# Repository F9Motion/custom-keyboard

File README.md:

# BEST KEYBOARD PROJECT EVER!!!

hey! this is text explaining what my awesome project is :)

here's an AWESOME screenshoot of my keyboard in action!

## HOW THIS WAS MADE

this custom keyboard was designed in [KiCad](https://www.kicad.org/) for the PCB, modeled in [Blender](https://www.blender.org/) for the 3D-printed enclosure, and runs on [CircuitPython](https://circuitpython.org/) :D

# Heres how to setup and flash the project :)
Clone the repository to your device:
git clone **https://github.com/f9motion/custom-keyboard**

Connect your microcontroller board in BOOTLOADER mode via USB

Copy the CircuitPython firmware files and keymap script to your device drive
firmware in my github repositorie ~~https://github.com/f9motion/custom-keyboard~~

Disconnect, plug in, and type away!
and be joyous!
# Sreenshots
**Schematic in KiCad:**

**PCB editor:**

**Case in blender 3.6**

#Bill Of Materials (BOM)

| Object name    | Cost   | Link                                                                                                                                                       |
|----------------|--------|------------------------------------------------------------------------------------------------------------------------------------------------------------|
| Soldering iron | $12.76 | https://aliexpress.ru/item/33052506638.html?spm=a2g2w.cart.cart_split.2.57294aa6AC23aP&sku_id=12000032616421342                                            |
| Stabilizers    | $9.00  | https://aliexpress.ru/item/1005006528731543.html?spm=a2g2w.cart.cart_split.4.182a4aa6UvSz3j&sku_id=12000039275106552                                       |
| Switchs        | $24.4  | https://aliexpress.ru/item/1005009446526905.html?spm=a2g2w.cart.cart_split.2.36c84aa6Uj1yYg&sku_id=12000049127519972                                       |
| Diodes x3      | $6.12  | https://aliexpress.ru/item/1005008957914820.html?spm=a2g2w.cart.cart_split.8.36c84aa6Uj1yYg&sku_id=12000047366893545                                       |
| Pico           | $2.2   | https://aliexpress.ru/item/1005003371056277.html?sku_id=12000035247643698                                                                                  |
| Solder         | $4.36  | https://aliexpress.ru/item/32889029087.html?shpMethod=AE_CN_SUPER_ECONOMY_G&sku_id=12000036063038181&spm=a2g2w.productlist.search_results.0.5a2f3831nIBAqg |
| Print PCB | $59.19 | 
| Filament price for 3d print  |                                        | WARNING: All price took from Bambu Studio!!!                                                                 |
| **Object name**     | **Weight** | **Cost**                                                                                                                                          |
| Case.step           | 153.95g    | $2.77                                                                                                                                             |
| keycaps.step        | 129.47g    | $2.59                                                                                                                                             |
| switch holder.step  | 29.67g     | $0.53                                                                                                                                             |
| TOTAL OF ALL: | | $123.92 |

AI DISCLOSURE
Ai helped me to now microcontroller name and how much u in shift ctrl etc (u is size) and helped to write firmware

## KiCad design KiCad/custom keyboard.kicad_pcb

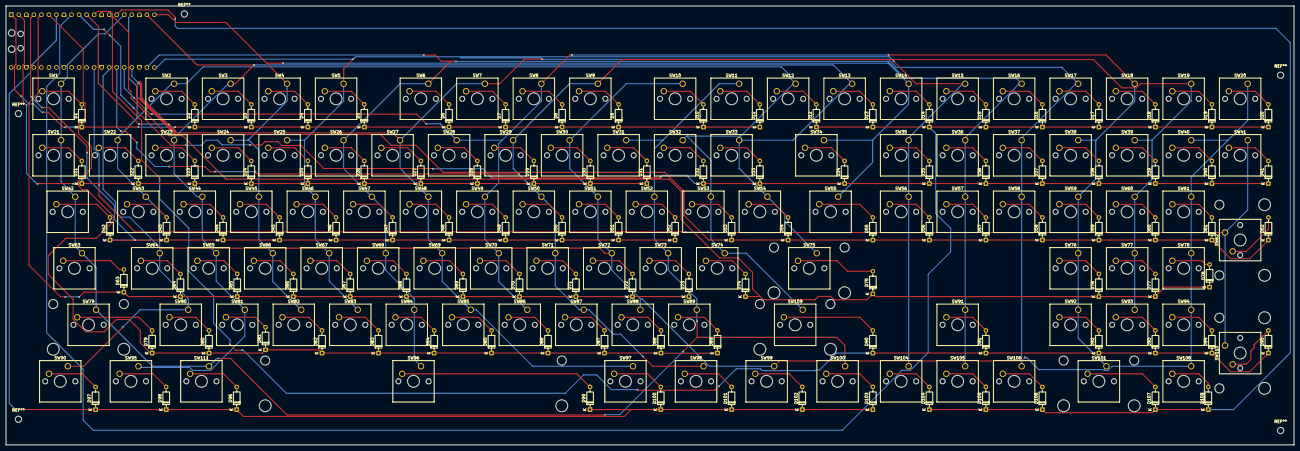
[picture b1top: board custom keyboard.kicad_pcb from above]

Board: 2 copper layers, 434.2 x 148.0 mm, 217 parts (1 on the bottom side), 131 nets.

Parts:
A1: RaspberryPi_Pico; RaspberryPi_Pico_Common_Unspecified
D1, D2, D3, D4, D5, D6, D7, D8, D9, D10, D11, D12, D13, D14, D15, D16, D17, D18, D19, D20, D21, D22, D23, D24, D25, D26, D27, D28, D29, D30, D31, D32, D33, D34, D35, D36, D37, D38, D39, D40, D41, D42, D43, D44, D45, D46, D47, D48, D49, D50, D51, D52, D53, D54, D55, D56, D57, D58, D59, D60, D61, D62, D63, D64, D65, D66, D67, D68, D69, D70, D71, D72, D73, D74, D75, D76, D77, D78, D79, D80, D81, D82, D83, D84, D85, D86, D87, D88, D89, D90, D91, D92, D93, D94, D95, D96, D97, D98, D99, D100, D101, D102, D103, D104, D105, D106, D107, D108: 1N4148; D_DO-35_SOD27_P7.62mm_Horizontal
SW1, SW2, SW3, SW4, SW5, SW6, SW7, SW8, SW9, SW10, SW11, SW12, SW13, SW14, SW15, SW16, SW17, SW18, SW19, SW20, SW21, SW22, SW23, SW24, SW25, SW26, SW27, SW28, SW29, SW30, SW31, SW32, SW33, SW34, SW35, SW36, SW37, SW38, SW39, SW40, SW41, SW43, SW44, SW45, SW46, SW47, SW48, SW49, SW50, SW51, SW52, SW53, SW54, SW56, SW57, SW58, SW59, SW60, SW61, SW64, SW65, SW66, SW67, SW68, SW69, SW70, SW71, SW72, SW73, SW74, SW76, SW77, SW78, SW80, SW81, SW82, SW83, SW84, SW85, SW86, SW87, SW88, SW89, SW91, SW92, SW93, SW94, SW104, SW105, SW106, SW108: SW_Push; SW_Cherry_MX_1.00u_PCB
SW42, SW55: SW_Push; SW_Cherry_MX_1.50u_PCB
SW62, SW101, SW110: SW_Push; SW_Cherry_MX_2.00u_PCB
SW63: SW_Push; SW_Cherry_MX_1.75u_PCB
SW75, SW79: SW_Push; SW_Cherry_MX_2.25u_PCB
SW90, SW95, SW97, SW98, SW99, SW100, SW111: SW_Push; SW_Cherry_MX_1.25u_PCB
SW96: SW_Push; SW_Cherry_MX_6.25u_PCB
SW109: SW_Push; SW_Cherry_MX_2.75u_PCB

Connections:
COL0: A1.16 (GPIO12), SW1.1, SW11.1, SW21.1, SW31.1, SW42.1, SW52.1, SW63.1, SW73.1, SW79.1, SW89.1, SW100.1, SW111.1
COL1: A1.17 (GPIO13), SW2.1, SW12.1, SW22.1, SW32.1, SW43.1, SW53.1, SW64.1, SW74.1, SW80.1, SW90.1, SW109.1
COL2: A1.19 (GPIO14), SW3.1, SW13.1, SW23.1, SW33.1, SW44.1, SW54.1, SW65.1, SW75.1, SW81.1, SW95.1
COL3: A1.20 (GPIO15), SW4.1, SW14.1, SW24.1, SW34.1, SW45.1, SW55.1, SW66.1, SW82.1
COL4: A1.21 (GPIO16), SW5.1, SW15.1, SW25.1, SW35.1, SW46.1, SW56.1, SW67.1, SW83.1, SW104.1
COL5: A1.22 (GPIO17), SW6.1, SW16.1, SW26.1, SW36.1, SW47.1, SW57.1, SW68.1, SW84.1, SW91.1, SW96.1, SW105.1
COL6: A1.24 (GPIO18), SW7.1, SW17.1, SW27.1, SW37.1, SW48.1, SW58.1, SW69.1, SW85.1, SW97.1, SW106.1
COL7: A1.25 (GPIO19), SW8.1, SW18.1, SW28.1, SW38.1, SW49.1, SW59.1, SW70.1, SW76.1, SW86.1, SW92.1, SW101.1
COL8: A1.26 (GPIO20), SW9.1, SW19.1, SW29.1, SW39.1, SW50.1, SW60.1, SW71.1, SW77.1, SW87.1, SW93.1, SW98.1
COL9: A1.27 (GPIO21), SW10.1, SW20.1, SW30.1, SW40.1, SW51.1, SW61.1, SW72.1, SW78.1, SW88.1, SW94.1, SW99.1, SW108.1
COL10: A1.29 (GPIO22), SW41.1, SW62.1, SW110.1
unnamed: D1.2 (A), SW1.2
unnamed: D2.2 (A), SW2.2
unnamed: D3.2 (A), SW3.2
unnamed: D4.2 (A), SW4.2
unnamed: D5.2 (A), SW5.2
unnamed: D6.2 (A), SW6.2
unnamed: D7.2 (A), SW7.2
unnamed: D8.2 (A), SW8.2
unnamed: D9.2 (A), SW9.2
unnamed: D10.2 (A), SW10.2
unnamed: D11.2 (A), SW11.2
unnamed: D12.2 (A), SW12.2
unnamed: D13.2 (A), SW13.2
unnamed: D14.2 (A), SW14.2
unnamed: D15.2 (A), SW15.2
unnamed: D16.2 (A), SW16.2
unnamed: D17.2 (A), SW17.2
unnamed: D18.2 (A), SW18.2
unnamed: D19.2 (A), SW19.2
unnamed: D20.2 (A), SW20.2
unnamed: D21.2 (A), SW21.2
unnamed: D22.2 (A), SW22.2
unnamed: D23.2 (A), SW23.2
unnamed: D24.2 (A), SW24.2
unnamed: D25.2 (A), SW25.2
unnamed: D26.2 (A), SW26.2
unnamed: D27.2 (A), SW27.2
unnamed: D28.2 (A), SW28.2
unnamed: D29.2 (A), SW29.2
unnamed: D30.2 (A), SW30.2
unnamed: D31.2 (A), SW31.2
unnamed: D32.2 (A), SW32.2
unnamed: D33.2 (A), SW33.2
unnamed: D34.2 (A), SW34.2
unnamed: D35.2 (A), SW35.2
unnamed: D36.2 (A), SW36.2
unnamed: D37.2 (A), SW37.2
unnamed: D38.2 (A), SW38.2
unnamed: D39.2 (A), SW39.2
unnamed: D40.2 (A), SW40.2
unnamed: D41.2 (A), SW41.2
unnamed: D42.2 (A), SW42.2
unnamed: D43.2 (A), SW43.2
unnamed: D44.2 (A), SW44.2
unnamed: D45.2 (A), SW45.2
unnamed: D46.2 (A), SW46.2
unnamed: D47.2 (A), SW47.2
unnamed: D48.2 (A), SW48.2
unnamed: D49.2 (A), SW49.2
unnamed: D50.2 (A), SW50.2
unnamed: D51.2 (A), SW51.2
unnamed: D52.2 (A), SW52.2
unnamed: D53.2 (A), SW53.2
unnamed: D54.2 (A), SW54.2
unnamed: D55.2 (A), SW55.2
unnamed: D56.2 (A), SW56.2
unnamed: D57.2 (A), SW57.2
unnamed: D58.2 (A), SW58.2
unnamed: D59.2 (A), SW59.2
unnamed: D60.2 (A), SW60.2
unnamed: D61.2 (A), SW61.2
unnamed: D62.2 (A), SW62.2
unnamed: D63.2 (A), SW63.2
unnamed: D64.2 (A), SW64.2
unnamed: D65.2 (A), SW65.2
unnamed: D66.2 (A), SW66.2
unnamed: D67.2 (A), SW67.2
unnamed: D68.2 (A), SW68.2
unnamed: D69.2 (A), SW69.2
unnamed: D70.2 (A), SW70.2
unnamed: D71.2 (A), SW71.2
unnamed: D72.2 (A), SW72.2
unnamed: D73.2 (A), SW73.2
unnamed: D74.2 (A), SW74.2
unnamed: D75.2 (A), SW75.2
unnamed: D76.2 (A), SW76.2
unnamed: D77.2 (A), SW77.2
unnamed: D78.2 (A), SW78.2
unnamed: D79.2 (A), SW79.2
unnamed: D80.2 (A), SW80.2
unnamed: D81.2 (A), SW81.2
unnamed: D82.2 (A), SW82.2
unnamed: D83.2 (A), SW83.2
unnamed: D84.2 (A), SW84.2
unnamed: D85.2 (A), SW85.2
unnamed: D86.2 (A), SW86.2
unnamed: D87.2 (A), SW87.2
unnamed: D88.2 (A), SW88.2
unnamed: D89.2 (A), SW89.2
unnamed: D90.2 (A), SW109.2
unnamed: D91.2 (A), SW91.2
unnamed: D92.2 (A), SW92.2
unnamed: D93.2 (A), SW93.2
unnamed: D94.2 (A), SW94.2
unnamed: D95.2 (A), SW110.2
unnamed: D96.2 (A), SW111.2
unnamed: D97.2 (A), SW90.2
unnamed: D98.2 (A), SW95.2
unnamed: D99.2 (A), SW96.2
unnamed: D100.2 (A), SW97.2
unnamed: D101.2 (A), SW98.2
unnamed: D102.2 (A), SW99.2
unnamed: D103.2 (A), SW100.2
unnamed: D104.2 (A), SW104.2
unnamed: D105.2 (A), SW105.2
unnamed: D106.2 (A), SW106.2
unnamed: D107.2 (A), SW101.2
unnamed: D108.2 (A), SW108.2
ROW0: A1.1 (GPIO0), D1.1 (K), D2.1 (K), D3.1 (K), D4.1 (K), D5.1 (K), D6.1 (K), D7.1 (K), D8.1 (K), D9.1 (K), D10.1 (K), D11.1 (K)
ROW1: A1.2 (GPIO1), D21.1 (K), D22.1 (K), D23.1 (K), D24.1 (K), D25.1 (K), D26.1 (K), D27.1 (K), D28.1 (K), D29.1 (K), D30.1 (K), D31.1 (K)
ROW2: A1.4 (GPIO2), D42.1 (K), D43.1 (K), D44.1 (K), D45.1 (K), D46.1 (K), D47.1 (K), D48.1 (K), D49.1 (K), D50.1 (K), D51.1 (K), D52.1 (K)
ROW3: A1.5 (GPIO3), D63.1 (K), D64.1 (K), D65.1 (K), D66.1 (K), D67.1 (K), D68.1 (K), D69.1 (K), D70.1 (K), D71.1 (K), D72.1 (K), D73.1 (K)
ROW4: A1.6 (GPIO4), D79.1 (K), D80.1 (K), D81.1 (K), D82.1 (K), D83.1 (K), D84.1 (K), D85.1 (K), D86.1 (K), D87.1 (K), D88.1 (K), D89.1 (K)
ROW5: A1.7 (GPIO5), D96.1 (K), D97.1 (K), D98.1 (K), D99.1 (K), D100.1 (K), D101.1 (K), D102.1 (K), D103.1 (K)
ROW6: A1.9 (GPIO6), D12.1 (K), D13.1 (K), D14.1 (K), D15.1 (K), D16.1 (K), D17.1 (K), D18.1 (K), D19.1 (K), D20.1 (K)
ROW7: A1.10 (GPIO7), D32.1 (K), D33.1 (K), D34.1 (K), D35.1 (K), D36.1 (K), D37.1 (K), D38.1 (K), D39.1 (K), D40.1 (K), D41.1 (K)
ROW8: A1.11 (GPIO8), D53.1 (K), D54.1 (K), D55.1 (K), D56.1 (K), D57.1 (K), D58.1 (K), D59.1 (K), D60.1 (K), D61.1 (K), D62.1 (K)
ROW9: A1.12 (GPIO9), D74.1 (K), D75.1 (K), D76.1 (K), D77.1 (K), D78.1 (K)
ROW10: A1.14 (GPIO10), D90.1 (K), D91.1 (K), D92.1 (K), D93.1 (K), D94.1 (K), D95.1 (K)
ROW11: A1.15 (GPIO11), D104.1 (K), D105.1 (K), D106.1 (K), D107.1 (K), D108.1 (K)
